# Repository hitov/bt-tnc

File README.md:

git submodule update --init

git submodule update --remote

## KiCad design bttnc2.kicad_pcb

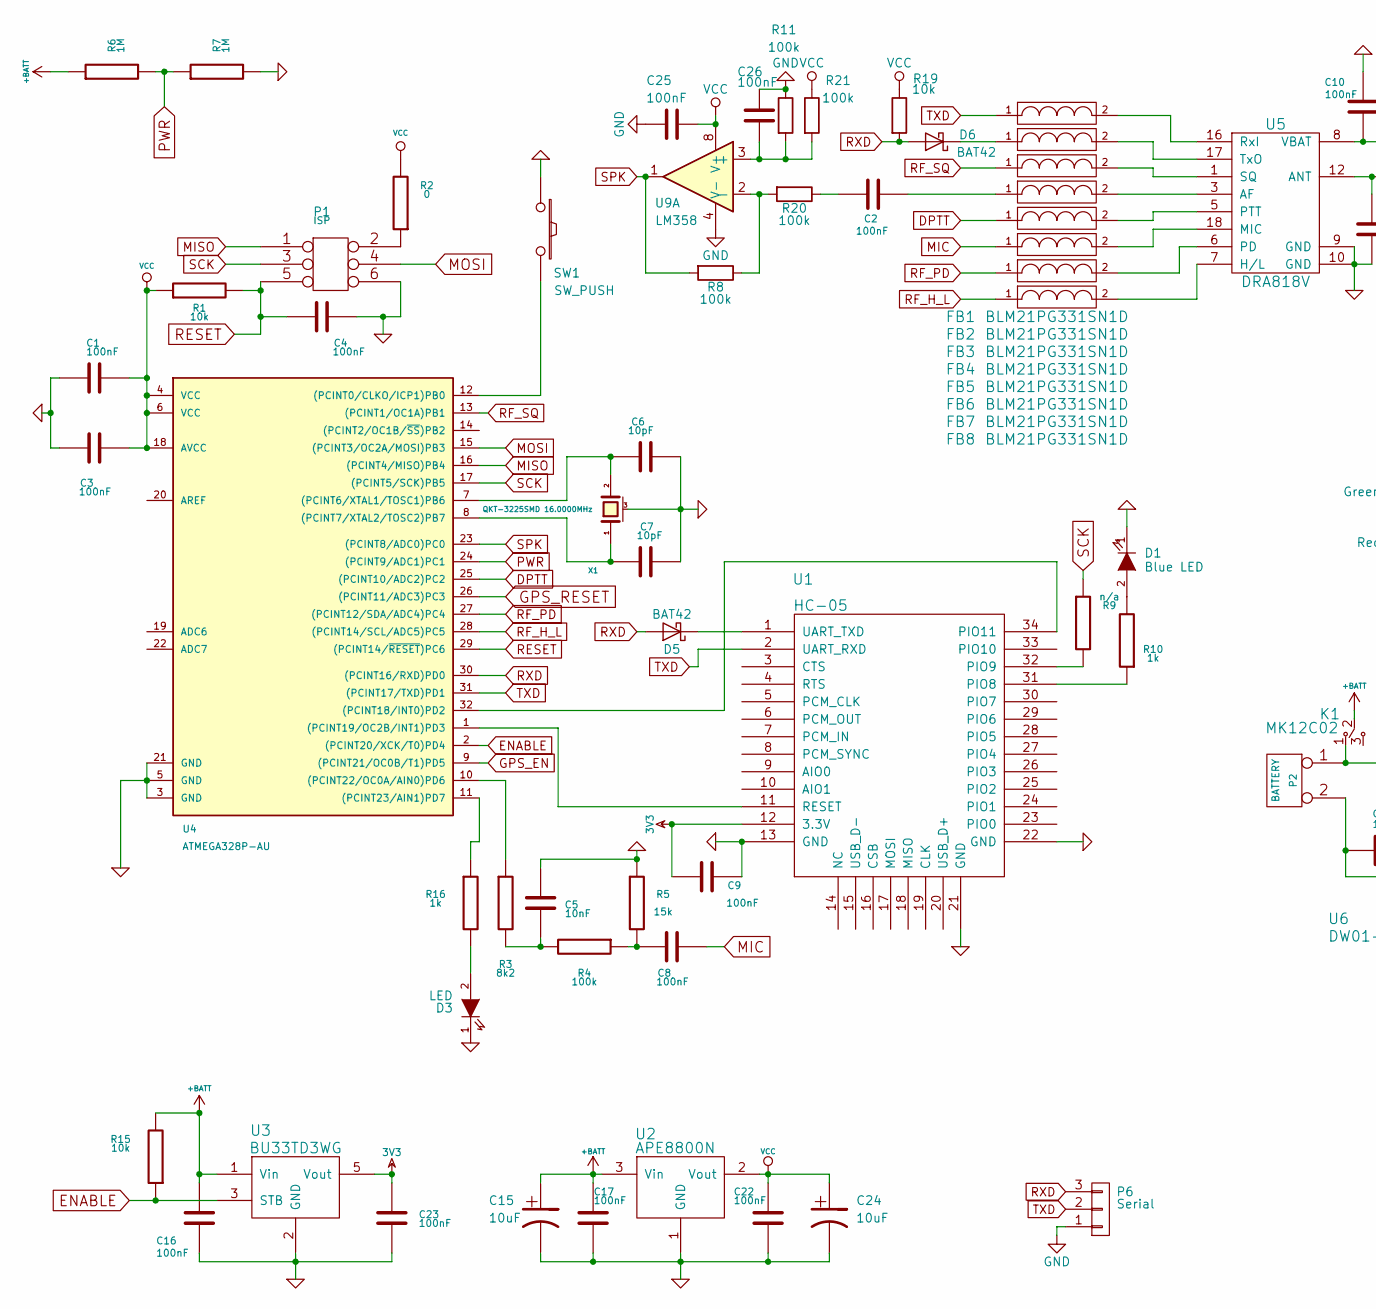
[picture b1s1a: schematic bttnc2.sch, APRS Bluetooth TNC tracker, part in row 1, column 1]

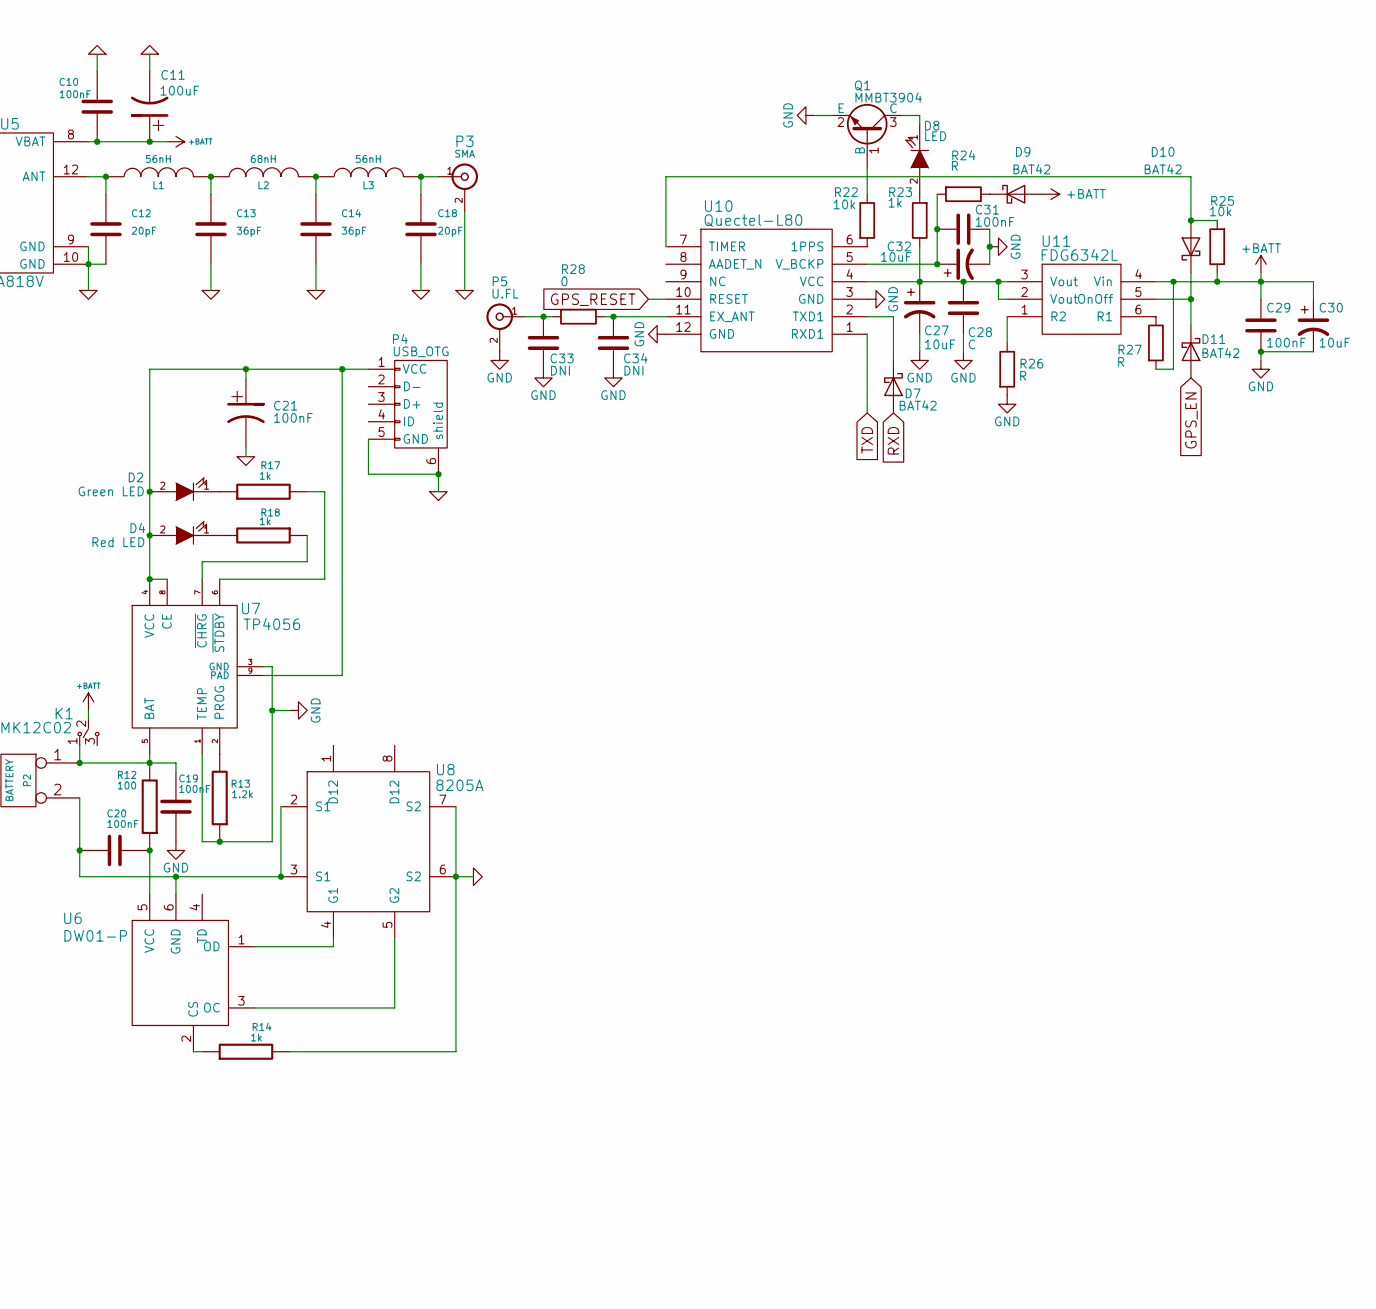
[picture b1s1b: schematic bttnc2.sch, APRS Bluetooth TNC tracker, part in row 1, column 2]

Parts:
C1, C2, C3, C4, C8, C9, C10, C16, C17, C19, C20, C21, C22, C23, C25, C26, C29, C31: 100nF; C_0805
C5: 10nF; C_0805
C6, C7: 10pF; C_0805
C11: 100uF; C_1210
C12, C18: 20pF; C_0805
C13, C14: 36pF; C_0805
C15, C24, C27, C30, C32: 10uF; C_1206
C28: C; C_0805
C33, C34: DNI; C_0805
D1: Blue LED; LED_0805
D2: Green LED; LED_0805
D3, D8: LED; LED_0805
D4: Red LED; LED_0805
D5, D6, D7, D9, D10, D11: BAT42; MiniMELF_Standard
FB1, FB2, FB3, FB4, FB5, FB6, FB7, FB8: BLM21PG331SN1D; C_0805
K1: MK12C02
L1, L3: 56nH; C_0805
L2: 68nH; C_0805
P1: ISP; Pin_Header_Straight_2x03_Pitch2.00mm
P2: BATTERY; JST_EH_B02B-EH-A_02x2.50mm_Straight
P3: SMA; CON-SMA-EDGE
P4: USB_OTG; USB_Micro-B
P5: U.FL; U.FL-Coax
P6: Serial; Pin_Header_Straight_1x03_Pitch2.54mm
Q1: MMBT3904; SOT-23
R1, R15, R19, R22, R25: 10k; R_0805
R2, R28: 0; R_0805
R3: 8k2; R_0805
R4, R8, R11, R20, R21: 100k; R_0805
R5: 15k; R_0805
R6, R7: 1M; R_0805
R9: n/a; R_0805
R10, R14, R16, R17, R18, R23: 1k; R_0805
R12: 100; R_0805
R13: 1.2k; R_0805
R24, R26, R27: R; R_0805
SW1: SW_PUSH; SW_Tactile_SPST_Angled
U1: HC-05
U2: APE8800N; SOT-23
U3: BU33TD3WG; SOT-23-5
U4: ATMEGA328P-AU; TQFP-32_7x7mm_Pitch0.8mm
U5: DRA818V; Dorji_DRA818
U6: DW01-P; SOT-23-6
U7: TP4056; SOIC-8-1EP_3.9x4.9mm_Pitch1.27mm
U8: 8205A; TSSOP-8_4.4x3mm_Pitch0.65mm
U9: LM358; SOIC-8-N
U10: Quectel-L80; Qectel-L80
U11: FDG6342L; SC-70-6
X1: QKT-3225SMD 16.0000MHz; crystal_FA238-TSX3225

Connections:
3V3: C9.1, C23.1, U1.12 (3.3V), U3.5 (Vout)
+BATT: C10.1, C11.1, C15.1, C16.1, C17.1, C29.1, C30.1, D9.2 (A), K1.2, R6.1, R15.2, R25.1, R27.2, U2.3 (Vin), U3.1 (Vin), U5.8 (VBAT), U11.4 (Vin)
DPTT: FB5.1, U4.25 ((PCINT10/ADC2)PC2)
ENABLE: R15.1, U3.3 (STB), U4.2 ((PCINT20/XCK/T0)PD4)
GND: C1.2, C3.1, C4.2, C5.2, C6.2, C7.2, C9.2, C10.2, C11.2, C12.2, C13.2, C14.2, C15.2, C16.2, C17.2, C18.2, C19.2, C21.2, C22.2, C23.2, C24.2, C25.2, C26.1, C27.2, C28.2, C29.2, C30.2, C31.1, C32.2, C33.2, C34.2, D1.1 (K), D3.1 (K), P1.6, P3.2 (Ext), P4.5 (GND), P4.6 (shield), P5.2 (Ext), P6.1, Q1.2 (E), R5.1, R7.2, R11.1, R13.1, R14.2, R26.2, SW1.1, U1.13 (GND), U1.21 (GND), U1.22 (GND), U2.1 (GND), U3.2 (GND), U4.3 (GND), U4.5 (GND), U4.21 (GND), U5.9 (GND), U5.10 (GND), U7.1 (TEMP), U7.3 (GND), U8.6 (S2), U8.7 (S2), U9.4 (V-), U10.3 (GND), U10.12 (GND), X1.3 (case)
GPS_EN: D11.2 (A), U4.9 ((PCINT21/OC0B/T1)PD5)
GPS_RESET: U4.26 ((PCINT11/ADC3)PC3), U10.10 (RESET)
MIC: C8.2, FB6.1
MISO: P1.1, U4.16 ((PCINT4/MISO)PB4)
MOSI: P1.4, U4.15 ((PCINT3/OC2A/MOSI)PB3)
unnamed: C2.1, R20.1
unnamed: C2.2, FB4.1
unnamed: C5.1, R3.2, R4.2
unnamed: C6.1, U4.7 ((PCINT6/XTAL1/TOSC1)PB6), X1.2
unnamed: C7.1, U4.8 ((PCINT7/XTAL2/TOSC2)PB7), X1.1
unnamed: C8.1, R4.1, R5.2
unnamed: C12.1, L1.1, U5.12 (ANT)
unnamed: C13.1, L1.2, L2.1
unnamed: C14.1, L2.2, L3.1
unnamed: C18.1, L3.2, P3.1 (In)
unnamed: C19.1, K1.1, P2.1, R12.2, U7.5 (BAT)
unnamed: C20.1, R12.1, U6.5 (VCC)
unnamed: C20.2, P2.2 (PM), U6.6 (GND), U8.2 (S1), U8.3 (S1)
unnamed: C21.1, D2.2 (A), D4.2 (A), P4.1 (VCC), U7.4 (VCC), U7.8 (CE), U7.9 (PAD)
unnamed: C26.2, R11.2, R21.2, U9.3 (+)
unnamed: C27.1, C28.1, R23.1, U10.4 (VCC), U11.2 (Vout), U11.3 (Vout)
unnamed: C31.2, C32.1, R24.2, U10.5 (V_BCKP)
unnamed: C33.1, P5.1 (In), R28.2
unnamed: C34.1, R28.1, U10.11 (EX_ANT)
unnamed: D1.2 (A), R10.2
unnamed: D2.1 (K), R17.1
unnamed: D3.2 (A), R16.2
unnamed: D4.1 (K), R18.2
unnamed: D5.1 (K), U1.1 (UART_TXD)
unnamed: D6.1 (K), FB2.1
unnamed: D7.1 (K), U10.2 (TXD1)
unnamed: D8.1 (K), Q1.3 (C)
unnamed: D8.2 (A), R23.2
unnamed: D9.1 (K), R24.1
unnamed: D10.1 (K), D11.1 (K), U11.5 (OnOff)
unnamed: D10.2 (A), R25.2, U10.7 (TIMER)
unnamed: FB1.2, U5.16 (RxI)
unnamed: FB2.2, U5.17 (TxO)
unnamed: FB3.2, U5.1 (SQ)
unnamed: FB4.2, U5.3 (AF)
unnamed: FB5.2, U5.5 (PTT)
unnamed: FB6.2, U5.18 (MIC)
unnamed: FB7.2, U5.6 (PD)
unnamed: FB8.2, U5.7 (H/L)
unnamed: P1.2, R2.1
unnamed: Q1.1 (B), R22.1
unnamed: R3.1, U4.10 ((PCINT22/OC0A/AIN0)PD6)
unnamed: R9.2, U1.32 (PIO9)
unnamed: R10.1, U1.31 (PIO8)
unnamed: R13.2, U7.2 (PROG)
unnamed: R14.1, U6.2 (CS)
unnamed: R16.1, U4.11 ((PCINT23/AIN1)PD7)
unnamed: R17.2, U7.6 (~STDBY)
unnamed: R18.1, U7.7 (~CHRG)
unnamed: R8.1, R20.2, U9.2 (-)
unnamed: R22.2, U10.6 (1PPS)
unnamed: R26.1, U11.1 (R2)
unnamed: R27.1, U11.6 (R1)
unnamed: SW1.2, U4.12 ((PCINT0/CLKO/ICP1)PB0)
unnamed: U1.11 (RESET), U4.1 ((PCINT19/OC2B/INT1)PD3)
unnamed: U1.34 (PIO11), U4.32 ((PCINT18/INT0)PD2)
unnamed: U6.1 (OD), U8.4 (G1)
unnamed: U6.3 (OC), U8.5 (G2)
PWR: R6.2, R7.1, U4.24 ((PCINT9/ADC1)PC1)
RESET: C4.1, P1.5, R1.2, U4.29 ((PCINT14/~RESET~)PC6)
RF_H_L: FB8.1, U4.28 ((PCINT14/SCL/ADC5)PC5)
RF_PD: FB7.1, U4.27 ((PCINT12/SDA/ADC4)PC4)
RF_SQ: FB3.1, U4.13 ((PCINT1/OC1A)PB1)
RXD: D5.2 (A), D6.2 (A), D7.2 (A), P6.3, R19.2, U4.30 ((PCINT16/RXD)PD0)
SCK: P1.3, R9.1, U4.17 ((PCINT5/SCK)PB5)
SPK: R8.2, U4.23 ((PCINT8/ADC0)PC0), U9.1
TXD: FB1.1, P6.2, U1.2 (UART_RXD), U4.31 ((PCINT17/TXD)PD1), U10.1 (RXD1)
VCC: C1.1, C3.2, C22.1, C24.1, C25.1, R1.1, R2.2, R19.1, R21.1, U2.2 (Vout), U4.4 (VCC), U4.6 (VCC), U4.18 (AVCC), U9.8 (V+)

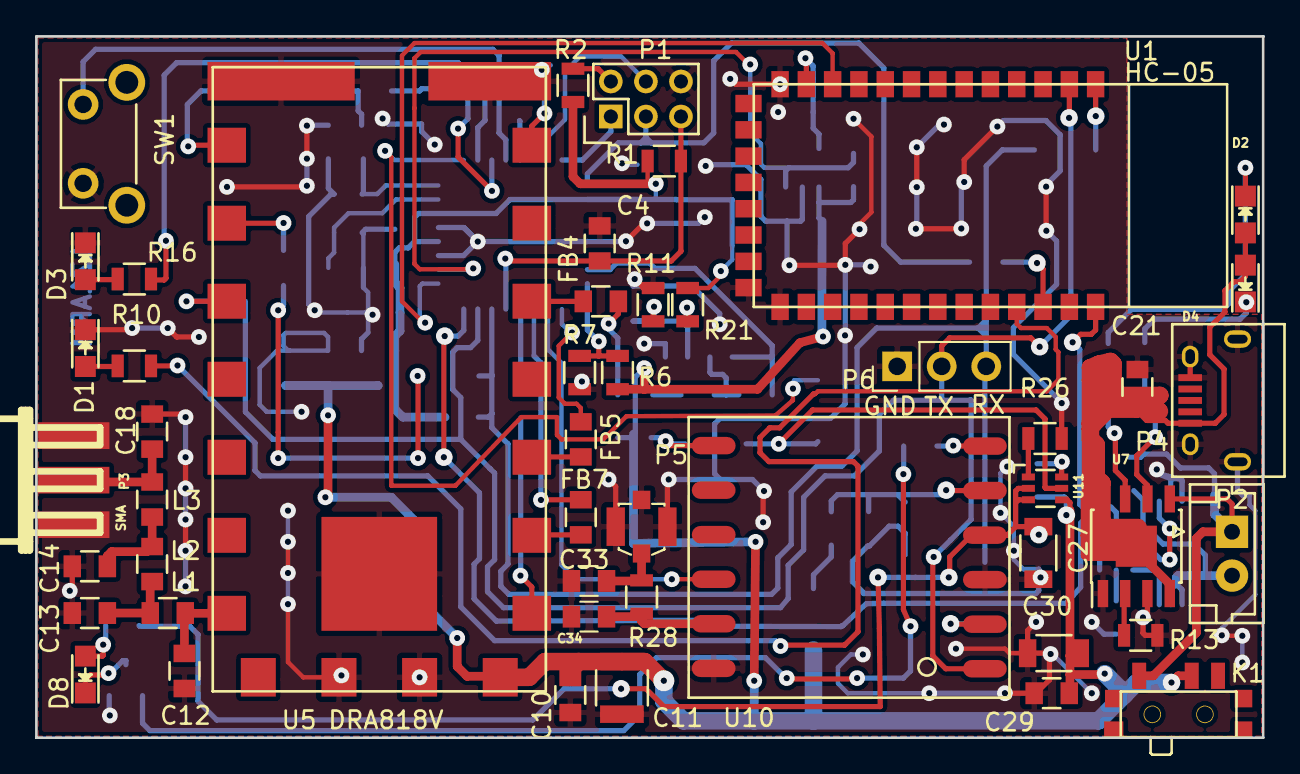
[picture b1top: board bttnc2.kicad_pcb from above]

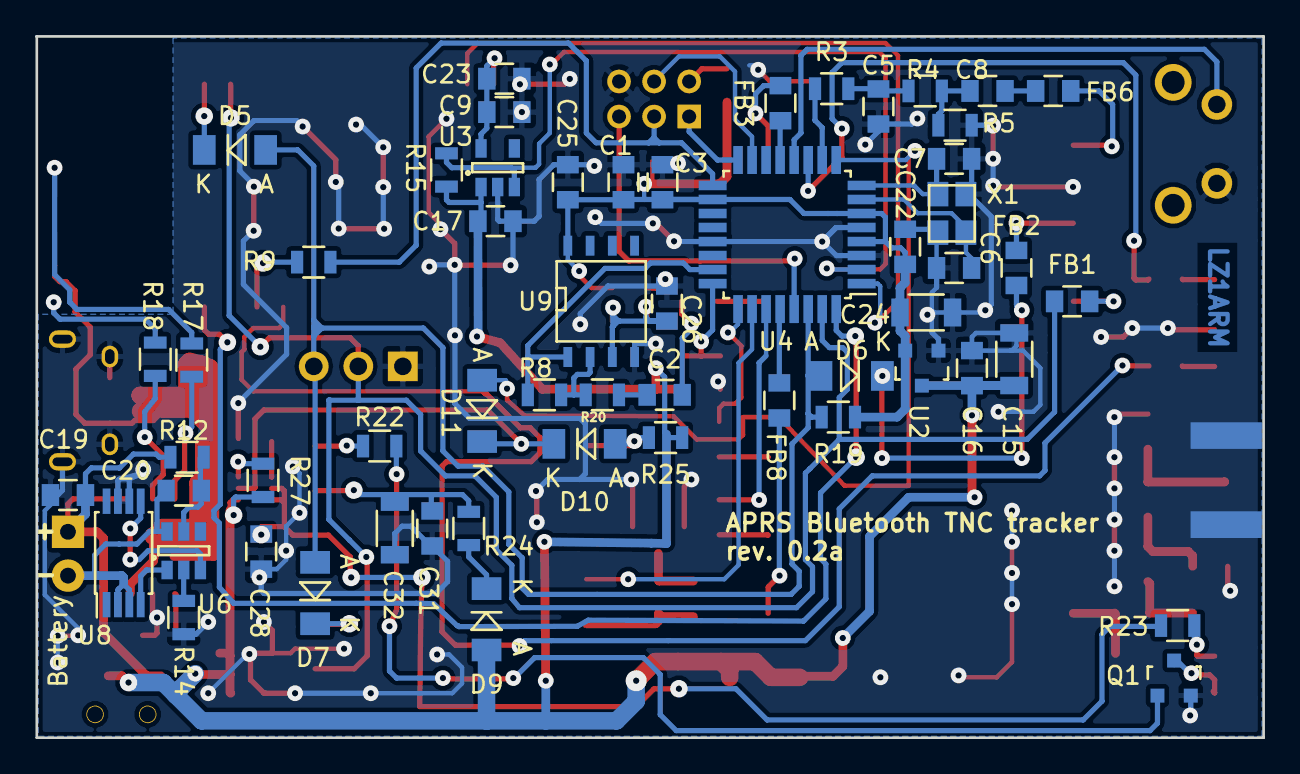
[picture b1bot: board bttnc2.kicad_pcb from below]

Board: 2 copper layers, 70.0 x 40.0 mm, 105 parts (57 on the bottom side), 78 nets.

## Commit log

2015-11-29 Bluetooth KISS TNC Kicad PCB - Initial commit
2015-11-29 Add kicad-radio-libraries as submodule
2015-11-29 Update component vaues
2015-11-29 Update gerber files and manufacture files
2015-11-29 Enable all layers
2016-11-26 Starting wrk on bttnc2
2016-11-26 Update kicad radio libraries
2016-12-05 Update bttnc project. Sch and Pcb files.
2016-12-05 Update schematics pdf
2016-12-05 Sch update - missing changes
2017-02-06 Latest updates
2017-02-08 Initial pcb routing
2017-02-09 Update pcb
2017-02-09 Updated SMA connector
2017-02-10 Add submodules branch
2017-02-10 Add readme file
2017-02-10 Add bttnc-rescue library
2017-02-10 Add AerodyneLabs/KiCadLib submodule
2017-02-10 Add bttnc2-cache.lib needed by eeschema
2017-02-10 Improve ground planes
2017-02-11 PCB reference labels rearrange
2017-02-11 Update and rearrange labels
2017-02-13 Update schematics and pcb
2017-02-13 Generate gerber files
2017-02-13 Gerber files update
2017-03-05 Export 3D models and add enclosure 3d design
2017-03-16 Add BOM file
2017-03-18 Schematics component values update
2017-03-18 Update component values in PCB and export BOM
2017-04-12 Update elements values
    This values was changed at device bring up.
    We have working hardware configuration.
2017-04-12 Export schematics pdf
